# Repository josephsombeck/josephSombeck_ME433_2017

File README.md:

# josephSombeck_ME433_2017
Repository for ME 433 class
Joseph Sombeck 03/27/2017

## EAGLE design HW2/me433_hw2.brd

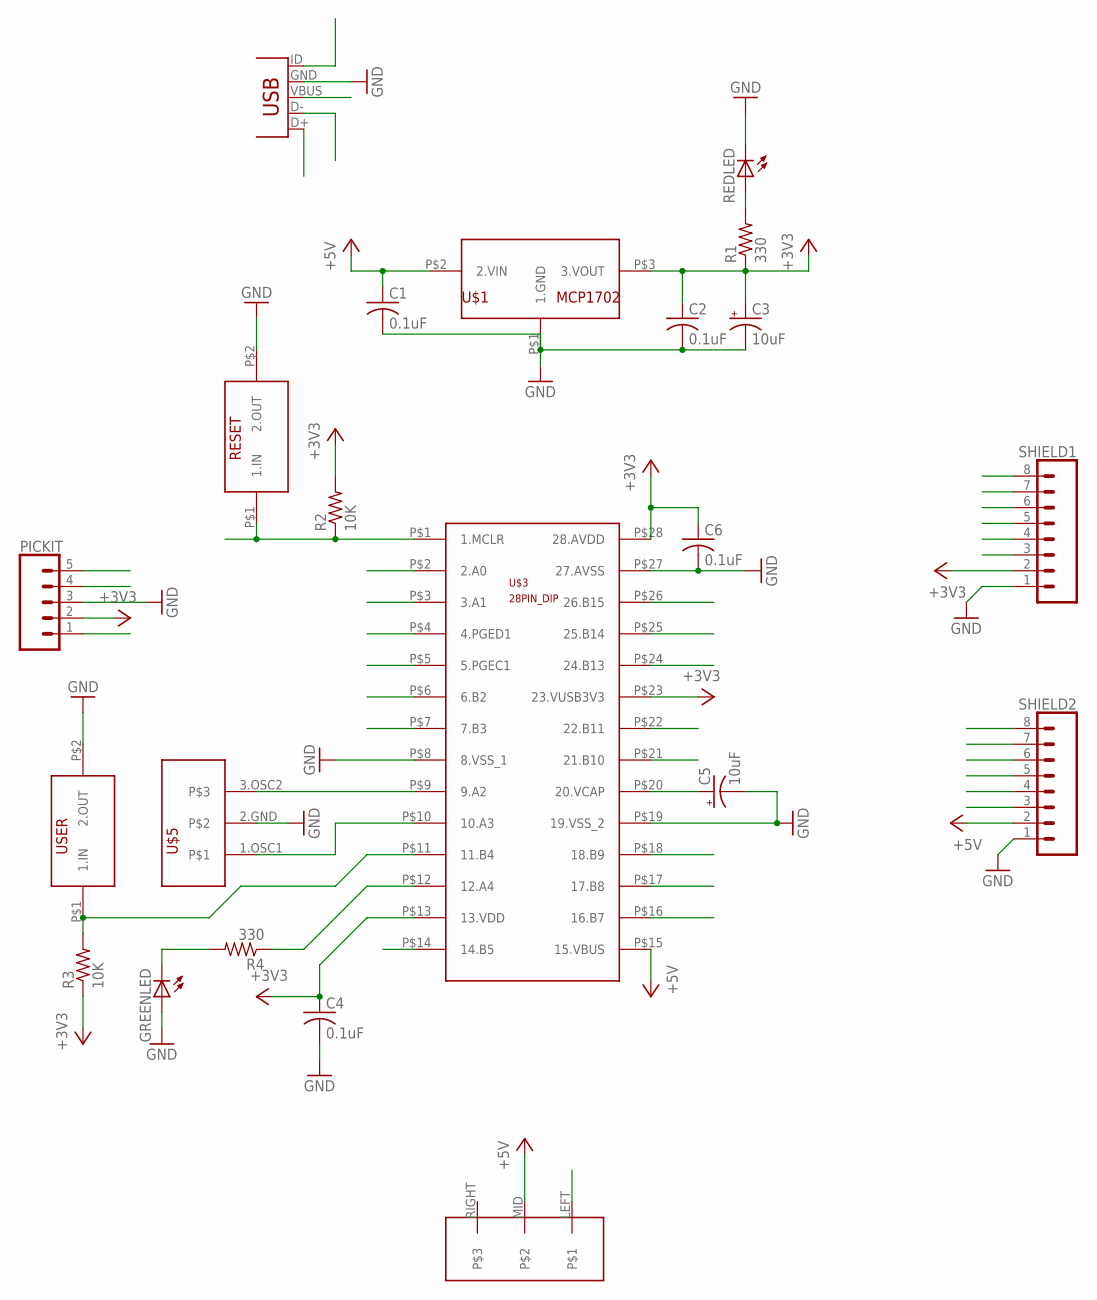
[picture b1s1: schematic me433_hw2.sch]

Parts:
C1, C2, C4, C6: 0.1uF; C025-030X050
C3, C5: 10uF; B45181B
GREENLED: LED3MM
PICKIT: CONN_05; 1X05
R1, R4: 330; 0207/10
R2, R3: 10K; 0207/10
REDLED: LED3MM
RESET: PUSH_BUTTON
SHIELD1, SHIELD2: CONN_08"; 1X08
U$1: MCP1702
U$2: USBMINIB; USB-MB-H
U$3: 28PIN_DIP
U$4: SLIDE_SWITCH
U$5: RESONATOR
USER: PUSH_BUTTON

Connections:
+3V3: C2.1, C3.+, C4.1, C6.1, PICKIT.2, R1.1, R2.2, R3.1, SHIELD1.2, U$1.P$3 (3.VOUT), U$3.P$13 (13.VDD), U$3.P$23 (23.VUSB3V3), U$3.P$28 (28.AVDD)
+5V: C1.1, SHIELD2.2, U$1.P$2 (2.VIN), U$3.P$15 (15.VBUS), U$4.MID
A0: SHIELD1.8, U$3.P$2 (2.A0)
A1: SHIELD1.7, U$3.P$3 (3.A1)
A4: R4.1, SHIELD1.3, U$3.P$12 (12.A4)
B2: SHIELD1.6, U$3.P$6 (6.B2)
B3: SHIELD1.5, U$3.P$7 (7.B3)
B4: R3.2, SHIELD1.4, U$3.P$11 (11.B4), USER.P$1 (1.IN)
B7: SHIELD2.3, U$3.P$16 (16.B7)
B8: SHIELD2.4, U$3.P$17 (17.B8)
B9: SHIELD2.5, U$3.P$18 (18.B9)
B13: SHIELD2.6, U$3.P$24 (24.B13)
B14: SHIELD2.7, U$3.P$25 (25.B14)
B15: SHIELD2.8, U$3.P$26 (26.B15)
D+: U$2.D+, U$3.P$21 (21.B10)
D-: U$2.D-, U$3.P$22 (22.B11)
GND: C1.2, C2.2, C3.-, C4.2, C5.-, C6.2, GREENLED.A, PICKIT.3, REDLED.K (C), RESET.P$2 (2.OUT), SHIELD1.1, SHIELD2.1, U$1.P$1 (1.GND), U$2.GND, U$3.P$8 (8.VSS_1), U$3.P$19 (19.VSS_2), U$3.P$27 (27.AVSS), U$5.2.GND, USER.P$2 (2.OUT)
MCLR: PICKIT.1, R2.1, RESET.P$1 (1.IN), U$3.P$1 (1.MCLR)
unnamed: R1.2, REDLED.A
unnamed: U$3.P$9 (9.A2), U$5.3.OSC2
unnamed: U$3.P$10 (10.A3), U$5.1.OSC1
unnamed: C5.+, U$3.P$20 (20.VCAP)
unnamed: GREENLED.K (C), R4.2
PGC1: PICKIT.5, U$3.P$5 (5.PGEC1)
PGD1: PICKIT.4, U$3.P$4 (4.PGED1)
SLIDESWITCH: U$2.VBUS, U$4.LEFT
USBID: U$2.ID (USBID), U$3.P$14 (14.B5)

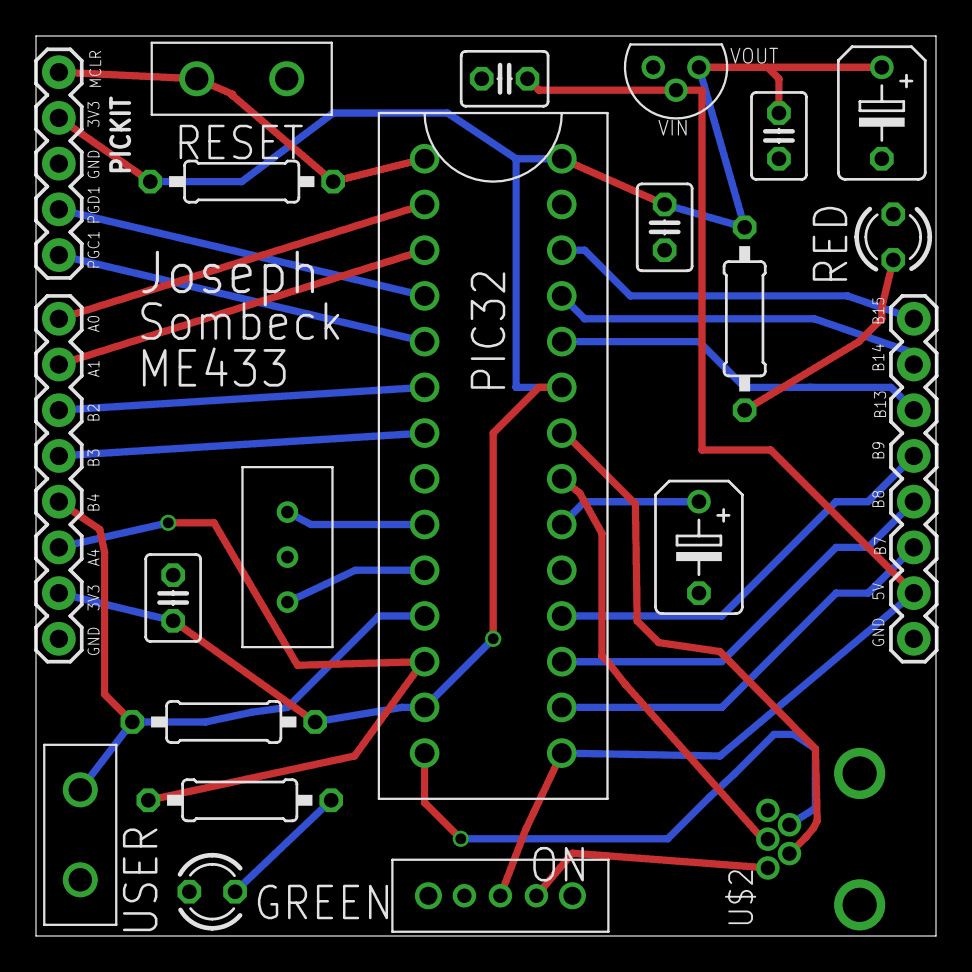
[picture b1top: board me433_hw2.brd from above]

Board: 2 copper layers, 50.0 x 50.0 mm, 22 parts (0 on the bottom side), 27 nets.

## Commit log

2017-03-27 Hello World
2017-03-28 made HW1 main file and folder
2017-03-28 first pass at pragmas
2017-03-28 blinking light test, not correct frequency
2017-03-28 led flashing at proper frequency and button added
2017-03-29 added images
2017-04-02 hw2, eagle pcb and schematic
2017-04-02 add .lbr files
2017-04-04 added ground plane and fixed things
2017-04-05 finished pcb and gerber files
2017-04-10 did hw4
2017-04-12 mcp23008 expander code included
2017-04-12 added video and circuit diagram
2017-04-16 LCD screen working
2017-04-16 lcd video
2017-04-16 fixed video
2017-04-20 imu and video
2017-04-24 hw8, lcd screen using harmony
2017-04-24 vidoe
2017-04-29 hw9 all
2017-04-29 hw1- code
2017-05-02 video hw10
2017-05-04 hw11 and video
2017-05-09 hw12
2017-05-09 hw13
2017-05-20 hw14 android usb app
2017-05-20 video of android USB app
2017-06-05 hw 15 files
2017-06-05 HW 18 plus some final project stuff
2017-06-05 hw19 and other stuff
2017-06-06 hw 16 and 17 pictures

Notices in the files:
parts and their libraries:
SparkFun-Connectors: Licensing: Creative Commons ShareAlike 4.0 International - https://creativecommons.org/licenses/by-sa/4.0
